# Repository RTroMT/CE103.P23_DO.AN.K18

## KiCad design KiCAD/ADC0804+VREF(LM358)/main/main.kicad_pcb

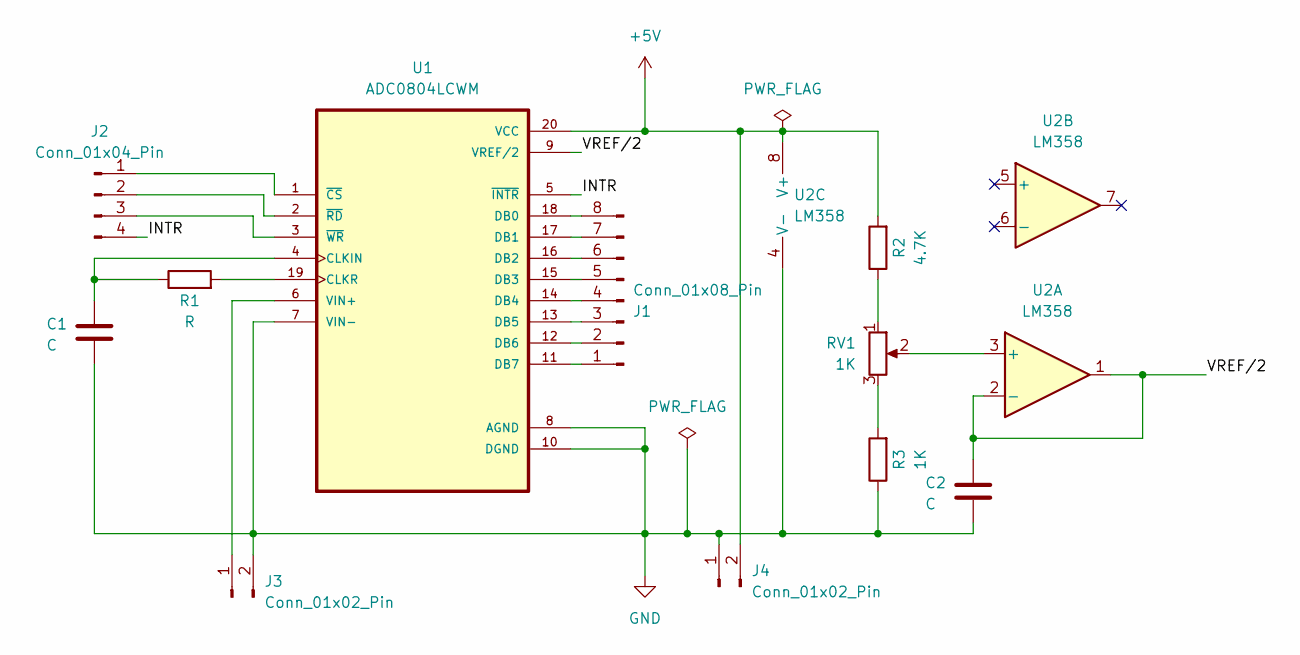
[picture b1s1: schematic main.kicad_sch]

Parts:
C1, C2: C; C_Disc_D5.0mm_W2.5mm_P2.50mm
J1: Conn_01x08_Pin; PinHeader_1x08_P2.54mm_Vertical
J2: Conn_01x04_Pin; PinHeader_1x04_P2.54mm_Vertical
J3, J4: Conn_01x02_Pin; PinHeader_1x02_P2.54mm_Vertical
R1: R; R_Axial_DIN0207_L6.3mm_D2.5mm_P7.62mm_Horizontal
R2: 4.7K; R_Axial_DIN0207_L6.3mm_D2.5mm_P7.62mm_Horizontal
R3: 1K; R_Axial_DIN0207_L6.3mm_D2.5mm_P7.62mm_Horizontal
RV1: 1K; Potentiometer_Bourns_3299W_Vertical
U1: ADC0804LCWM; DIP-20_W7.62mm
U2: LM358; DIP-8_W7.62mm

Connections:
+5V: J4.2, R2.2, U1.20 (VCC), U2.8 (V+)
/INTR: J2.4, U1.5 (~INTR)
/VREF/2: C2.1, U1.9 (VREF/2), U2.1, U2.2 (-)
GND: C1.2, C2.2, J3.2, J4.1, R3.1, U1.7 (VIN-), U1.8 (AGND), U1.10 (DGND), U2.4 (V-)
unnamed: J1.1, U1.11 (DB7)
unnamed: J1.2, U1.12 (DB6)
unnamed: J1.3, U1.13 (DB5)
unnamed: J1.4, U1.14 (DB4)
unnamed: J1.5, U1.15 (DB3)
unnamed: J1.6, U1.16 (DB2)
unnamed: J1.7, U1.17 (DB1)
unnamed: J1.8, U1.18 (DB0)
unnamed: J2.1, U1.1 (~CS)
unnamed: J2.2, U1.2 (~RD)
unnamed: J2.3, U1.3 (~WR)
unnamed: J3.1, U1.6 (VIN+)
unnamed: R2.1, RV1.1
unnamed: R3.2, RV1.3
unnamed: C1.1, R1.1, U1.4 (CLKIN)
unnamed: R1.2, U1.19 (CLKR)
unnamed: RV1.2, U2.3 (+)

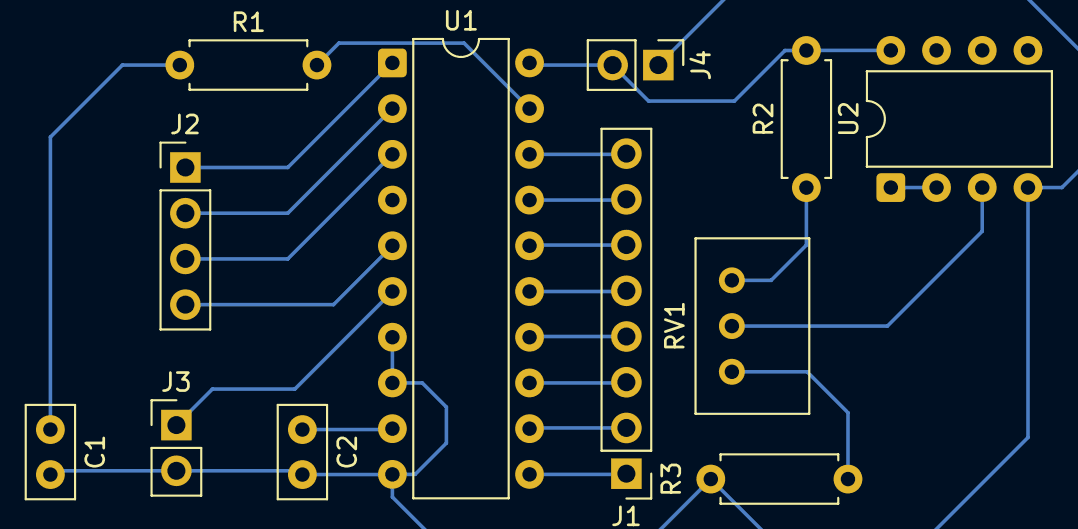
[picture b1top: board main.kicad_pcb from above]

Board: 2 copper layers, 12 parts (0 on the bottom side), 21 nets.

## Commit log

2025-05-14 Project complete V1.0
2025-05-14 Schematic fixed (Proteus)
2025-05-14 KiCad ADC0804 + LM358 schematic and PCB completed
2025-06-03 Code optimized
